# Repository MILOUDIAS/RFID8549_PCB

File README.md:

# RFID8549_PCB
PCB for bring-up testing of our RFID chip in ihp sg13g2 pdk

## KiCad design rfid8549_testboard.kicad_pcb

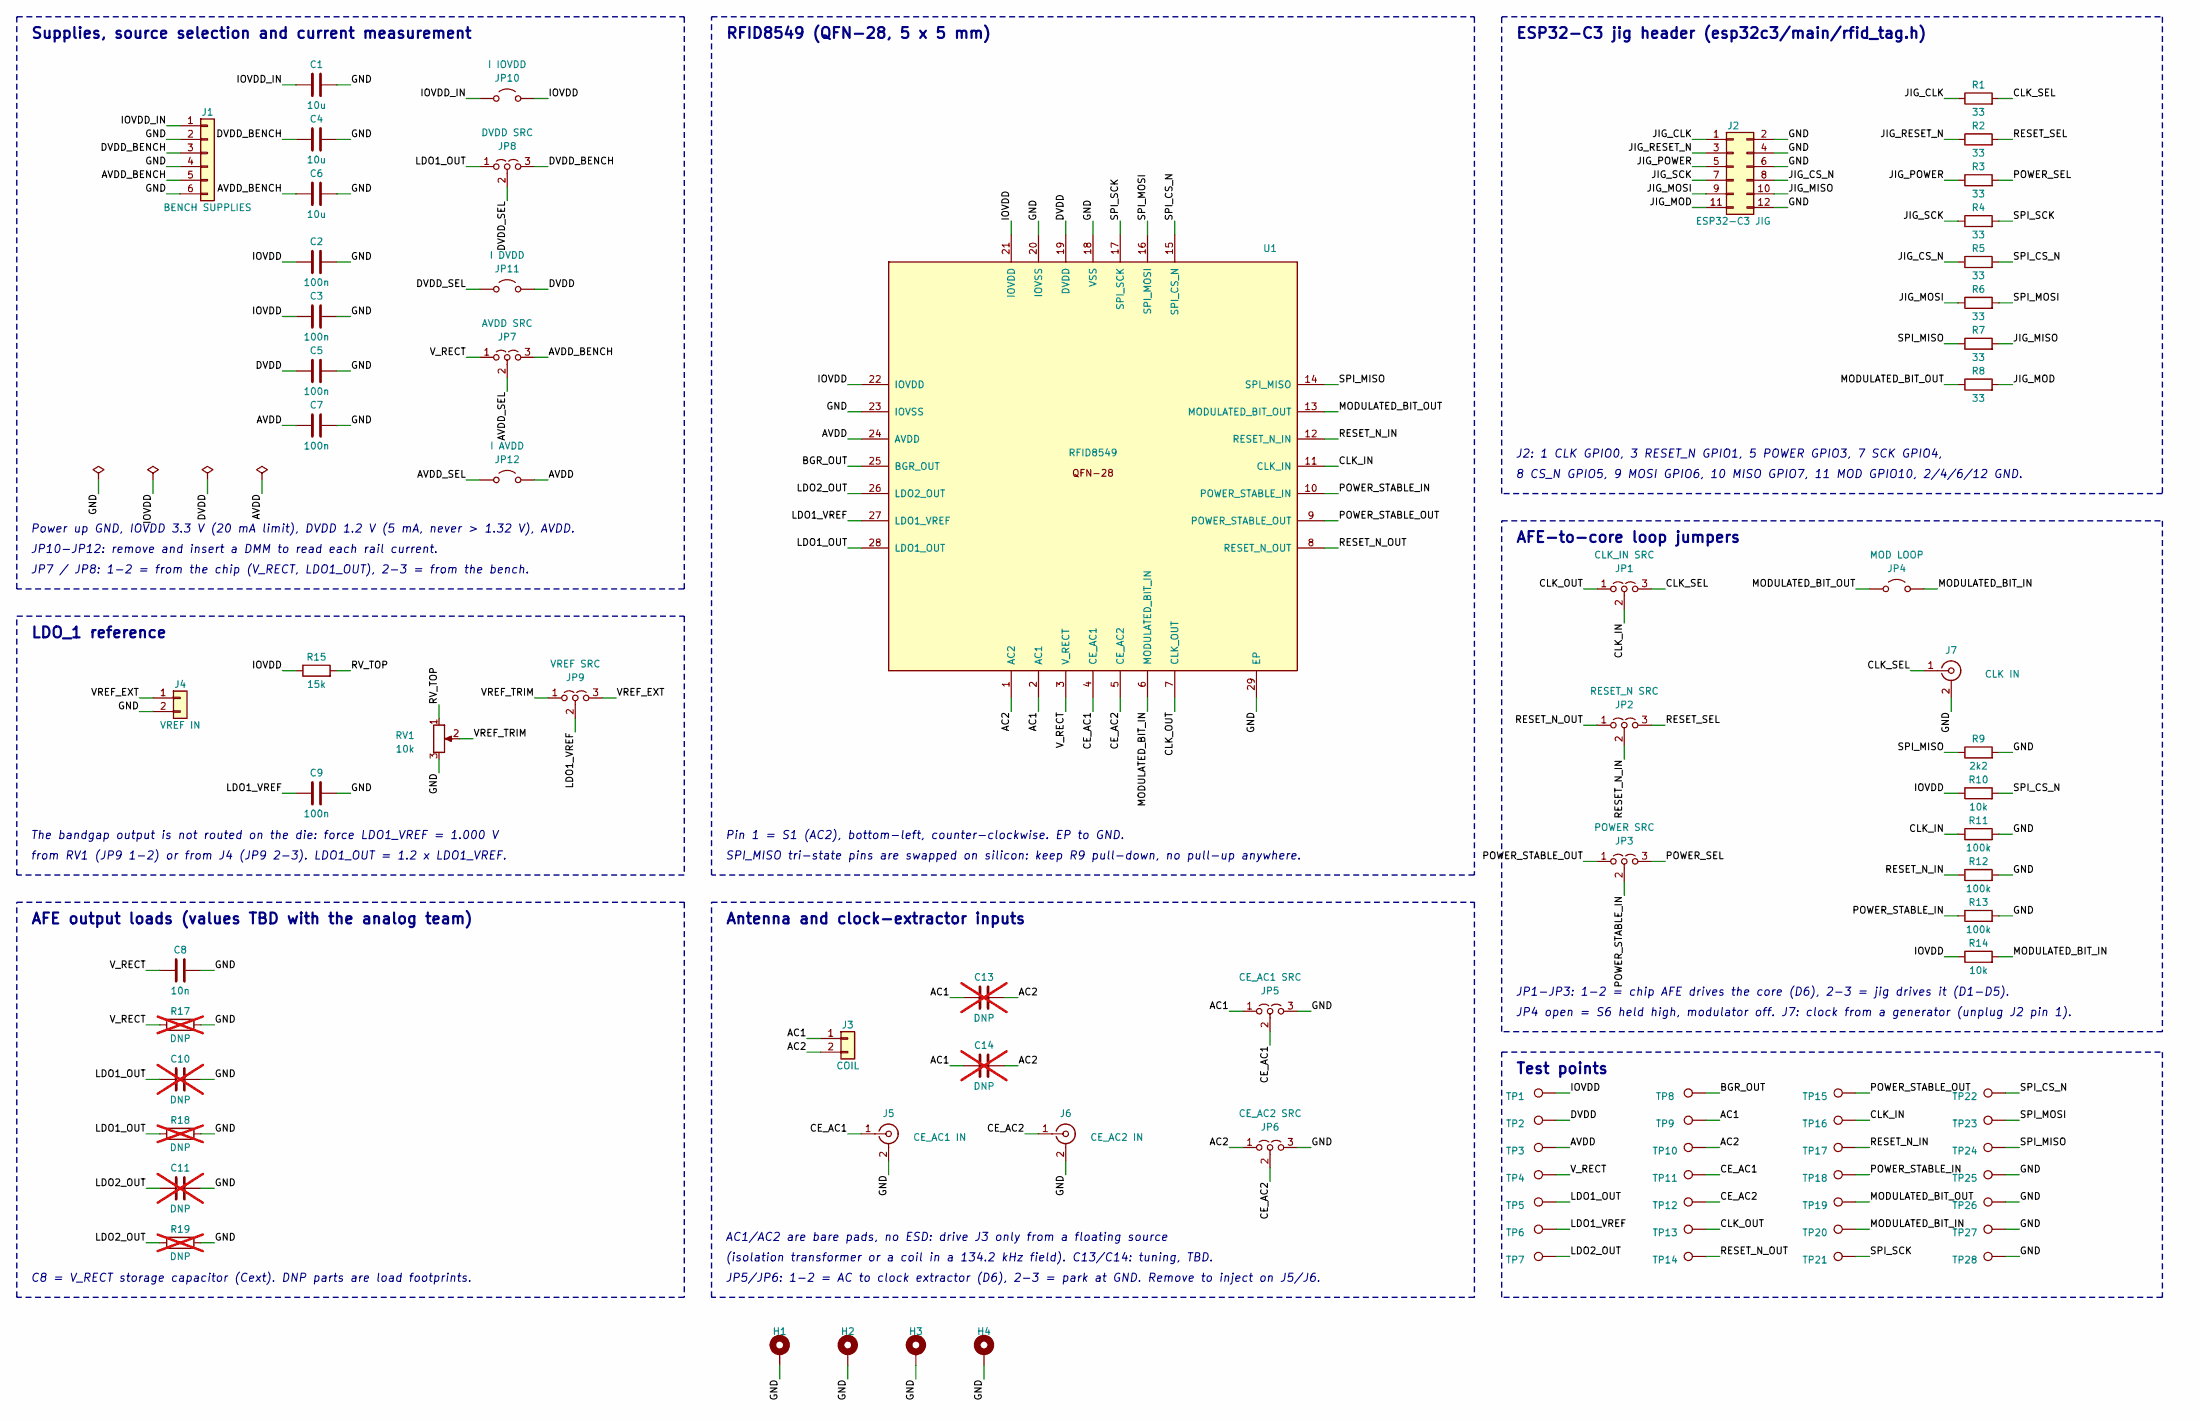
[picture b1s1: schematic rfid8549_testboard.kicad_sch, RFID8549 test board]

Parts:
C1, C4, C6: 10u; C_1206_3216Metric
C2, C3, C5, C7, C9: 100n; C_0805_2012Metric
C8: 10n; C_0805_2012Metric
C10, C11, C13, C14: DNP; C_0805_2012Metric; not fitted
H1, H2, H3, H4: M3; MountingHole_3.2mm_M3_Pad_Via
J1: BENCH SUPPLIES; TerminalBlock_Phoenix_MKDS-1,5-6_1x06_P5.00mm_Horizontal
J2: ESP32-C3 JIG; PinHeader_2x06_P2.54mm_Vertical
J3: COIL; TerminalBlock_Phoenix_MKDS-1,5-2_1x02_P5.00mm_Horizontal
J4: VREF IN; PinHeader_1x02_P2.54mm_Vertical
J5: CE_AC1 IN; SMA_Amphenol_132134_Vertical
J6: CE_AC2 IN; SMA_Amphenol_132134_Vertical
J7: CLK IN; SMA_Amphenol_132134_Vertical
JP1: CLK_IN SRC; PinHeader_1x03_P2.54mm_Vertical
JP2: RESET_N SRC; PinHeader_1x03_P2.54mm_Vertical
JP3: POWER SRC; PinHeader_1x03_P2.54mm_Vertical
JP4: MOD LOOP; PinHeader_1x02_P2.54mm_Vertical
JP5: CE_AC1 SRC; PinHeader_1x03_P2.54mm_Vertical
JP6: CE_AC2 SRC; PinHeader_1x03_P2.54mm_Vertical
JP7: AVDD SRC; PinHeader_1x03_P2.54mm_Vertical
JP8: DVDD SRC; PinHeader_1x03_P2.54mm_Vertical
JP9: VREF SRC; PinHeader_1x03_P2.54mm_Vertical
JP10: I IOVDD; PinHeader_1x02_P2.54mm_Vertical
JP11: I DVDD; PinHeader_1x02_P2.54mm_Vertical
JP12: I AVDD; PinHeader_1x02_P2.54mm_Vertical
R1, R2, R3, R4, R5, R6, R7, R8: 33; R_0805_2012Metric
R9: 2k2; R_0805_2012Metric
R10, R14: 10k; R_0805_2012Metric
R11, R12, R13: 100k; R_0805_2012Metric
R15: 15k; R_0805_2012Metric
R17, R18, R19: DNP; R_0805_2012Metric; not fitted
RV1: 10k; Potentiometer_Bourns_3296W_Vertical
TP1: IOVDD; TestPoint_Keystone_5000-5004_Miniature
TP2: DVDD; TestPoint_Keystone_5000-5004_Miniature
TP3: AVDD; TestPoint_Keystone_5000-5004_Miniature
TP4: V_RECT; TestPoint_Keystone_5000-5004_Miniature
TP5: LDO1_OUT; TestPoint_Keystone_5000-5004_Miniature
TP6: LDO1_VREF; TestPoint_Keystone_5000-5004_Miniature
TP7: LDO2_OUT; TestPoint_Keystone_5000-5004_Miniature
TP8: BGR_OUT; TestPoint_Keystone_5000-5004_Miniature
TP9: AC1; TestPoint_Keystone_5000-5004_Miniature
TP10: AC2; TestPoint_Keystone_5000-5004_Miniature
TP11: CE_AC1; TestPoint_Keystone_5000-5004_Miniature
TP12: CE_AC2; TestPoint_Keystone_5000-5004_Miniature
TP13: CLK_OUT; TestPoint_Keystone_5000-5004_Miniature
TP14: RESET_N_OUT; TestPoint_Keystone_5000-5004_Miniature
TP15: POWER_STABLE_OUT; TestPoint_Keystone_5000-5004_Miniature
TP16: CLK_IN; TestPoint_Keystone_5000-5004_Miniature
TP17: RESET_N_IN; TestPoint_Keystone_5000-5004_Miniature
TP18: POWER_STABLE_IN; TestPoint_Keystone_5000-5004_Miniature
TP19: MODULATED_BIT_OUT; TestPoint_Keystone_5000-5004_Miniature
TP20: MODULATED_BIT_IN; TestPoint_Keystone_5000-5004_Miniature
TP21: SPI_SCK; TestPoint_Keystone_5000-5004_Miniature
TP22: SPI_CS_N; TestPoint_Keystone_5000-5004_Miniature
TP23: SPI_MOSI; TestPoint_Keystone_5000-5004_Miniature
TP24: SPI_MISO; TestPoint_Keystone_5000-5004_Miniature
TP25, TP26, TP27, TP28: GND; TestPoint_Keystone_5000-5004_Miniature
U1: RFID8549; QFN-28-1EP_5x5mm_P0.5mm_EP3.35x3.35mm_ThermalVias

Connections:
AC1: C13.1, C14.1, J3.1, JP5.1 (A), TP9.1, U1.2 (AC1)
AC2: C13.2, C14.2, J3.2, JP6.1 (A), TP10.1, U1.1 (AC2)
AVDD: C7.1, JP12.2 (B), TP3.1, U1.24 (AVDD)
AVDD_BENCH: C6.1, J1.5, JP7.3 (B)
AVDD_SEL: JP7.2 (C), JP12.1 (A)
BGR_OUT: TP8.1, U1.25 (BGR_OUT)
CE_AC1: J5.1 (In), JP5.2 (C), TP11.1, U1.4 (CE_AC1)
CE_AC2: J6.1 (In), JP6.2 (C), TP12.1, U1.5 (CE_AC2)
CLK_IN: JP1.2 (C), R11.1, TP16.1, U1.11 (CLK_IN)
CLK_OUT: JP1.1 (A), TP13.1, U1.7 (CLK_OUT)
CLK_SEL: J7.1 (In), JP1.3 (B), R1.2
DVDD: C5.1, JP11.2 (B), TP2.1, U1.19 (DVDD)
DVDD_BENCH: C4.1, J1.3, JP8.3 (B)
DVDD_SEL: JP8.2 (C), JP11.1 (A)
GND: C1.2, C2.2, C3.2, C4.2, C5.2, C6.2, C7.2, C8.2, C9.2, C10.2, C11.2, H1.1, H2.1, H3.1, H4.1, J1.2, J1.4, J1.6, J2.2, J2.4, J2.6, J2.12, J4.2, J5.2 (Ext), J6.2 (Ext), J7.2 (Ext), JP5.3 (B), JP6.3 (B), R9.2, R11.2, R12.2, R13.2, R17.2, R18.2, R19.2, RV1.3, TP25.1, TP26.1, TP27.1, TP28.1, U1.18 (VSS), U1.20 (IOVSS), U1.23 (IOVSS), U1.29 (EP)
IOVDD: C2.1, C3.1, JP10.2 (B), R10.1, R14.1, R15.1, TP1.1, U1.21 (IOVDD), U1.22 (IOVDD)
IOVDD_IN: C1.1, J1.1, JP10.1 (A)
JIG_CLK: J2.1, R1.1
JIG_CS_N: J2.8, R5.1
JIG_MISO: J2.10, R7.2
JIG_MOD: J2.11, R8.2
JIG_MOSI: J2.9, R6.1
JIG_POWER: J2.5, R3.1
JIG_RESET_N: J2.3, R2.1
JIG_SCK: J2.7, R4.1
LDO1_OUT: C10.1, JP8.1 (A), R18.1, TP5.1, U1.28 (LDO1_OUT)
LDO1_VREF: C9.1, JP9.2 (C), TP6.1, U1.27 (LDO1_VREF)
LDO2_OUT: C11.1, R19.1, TP7.1, U1.26 (LDO2_OUT)
MODULATED_BIT_IN: JP4.2 (B), R14.2, TP20.1, U1.6 (MODULATED_BIT_IN)
MODULATED_BIT_OUT: JP4.1 (A), R8.1, TP19.1, U1.13 (MODULATED_BIT_OUT)
POWER_SEL: JP3.3 (B), R3.2
POWER_STABLE_IN: JP3.2 (C), R13.1, TP18.1, U1.10 (POWER_STABLE_IN)
POWER_STABLE_OUT: JP3.1 (A), TP15.1, U1.9 (POWER_STABLE_OUT)
RESET_N_IN: JP2.2 (C), R12.1, TP17.1, U1.12 (RESET_N_IN)
RESET_N_OUT: JP2.1 (A), TP14.1, U1.8 (RESET_N_OUT)
RESET_SEL: JP2.3 (B), R2.2
RV_TOP: R15.2, RV1.1
SPI_CS_N: R5.2, R10.2, TP22.1, U1.15 (SPI_CS_N)
SPI_MISO: R7.1, R9.1, TP24.1, U1.14 (SPI_MISO)
SPI_MOSI: R6.2, TP23.1, U1.16 (SPI_MOSI)
SPI_SCK: R4.2, TP21.1, U1.17 (SPI_SCK)
VREF_EXT: J4.1, JP9.3 (B)
VREF_TRIM: JP9.1 (A), RV1.2
V_RECT: C8.1, JP7.1 (A), R17.1, TP4.1, U1.3 (V_RECT)

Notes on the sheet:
Supplies, source selection and current measurement
Power up GND, IOVDD 3.3 V (20 mA limit), DVDD 1.2 V (5 mA, never > 1.32 V), AVDD.
JP10-JP12: remove and insert a DMM to read each rail current.
JP7 / JP8: 1-2 = from the chip (V_RECT, LDO1_OUT), 2-3 = from the bench.
LDO_1 reference
The bandgap output is not routed on the die: force LDO1_VREF = 1.000 V
from RV1 (JP9 1-2) or from J4 (JP9 2-3). LDO1_OUT = 1.2 x LDO1_VREF.
AFE output loads (values TBD with the analog team)
C8 = V_RECT storage capacitor (Cext). DNP parts are load footprints.
RFID8549 (QFN-28, 5 x 5 mm)
Pin 1 = S1 (AC2), bottom-left, counter-clockwise. EP to GND.
SPI_MISO tri-state pins are swapped on silicon: keep R9 pull-down, no pull-up anywhere.
Antenna and clock-extractor inputs
AC1/AC2 are bare pads, no ESD: drive J3 only from a floating source
(isolation transformer or a coil in a 134.2 kHz field). C13/C14: tuning, TBD.
JP5/JP6: 1-2 = AC to clock extractor (D6), 2-3 = park at GND. Remove to inject on J5/J6.
ESP32-C3 jig header (esp32c3/main/rfid_tag.h)
J2: 1 CLK GPIO0, 3 RESET_N GPIO1, 5 POWER GPIO3, 7 SCK GPIO4,
8 CS_N GPIO5, 9 MOSI GPIO6, 10 MISO GPIO7, 11 MOD GPIO10, 2/4/6/12 GND.
AFE-to-core loop jumpers
JP1-JP3: 1-2 = chip AFE drives the core (D6), 2-3 = jig drives it (D1-D5).
JP4 open = S6 held high, modulator off. J7: clock from a generator (unplug J2 pin 1).
Test points

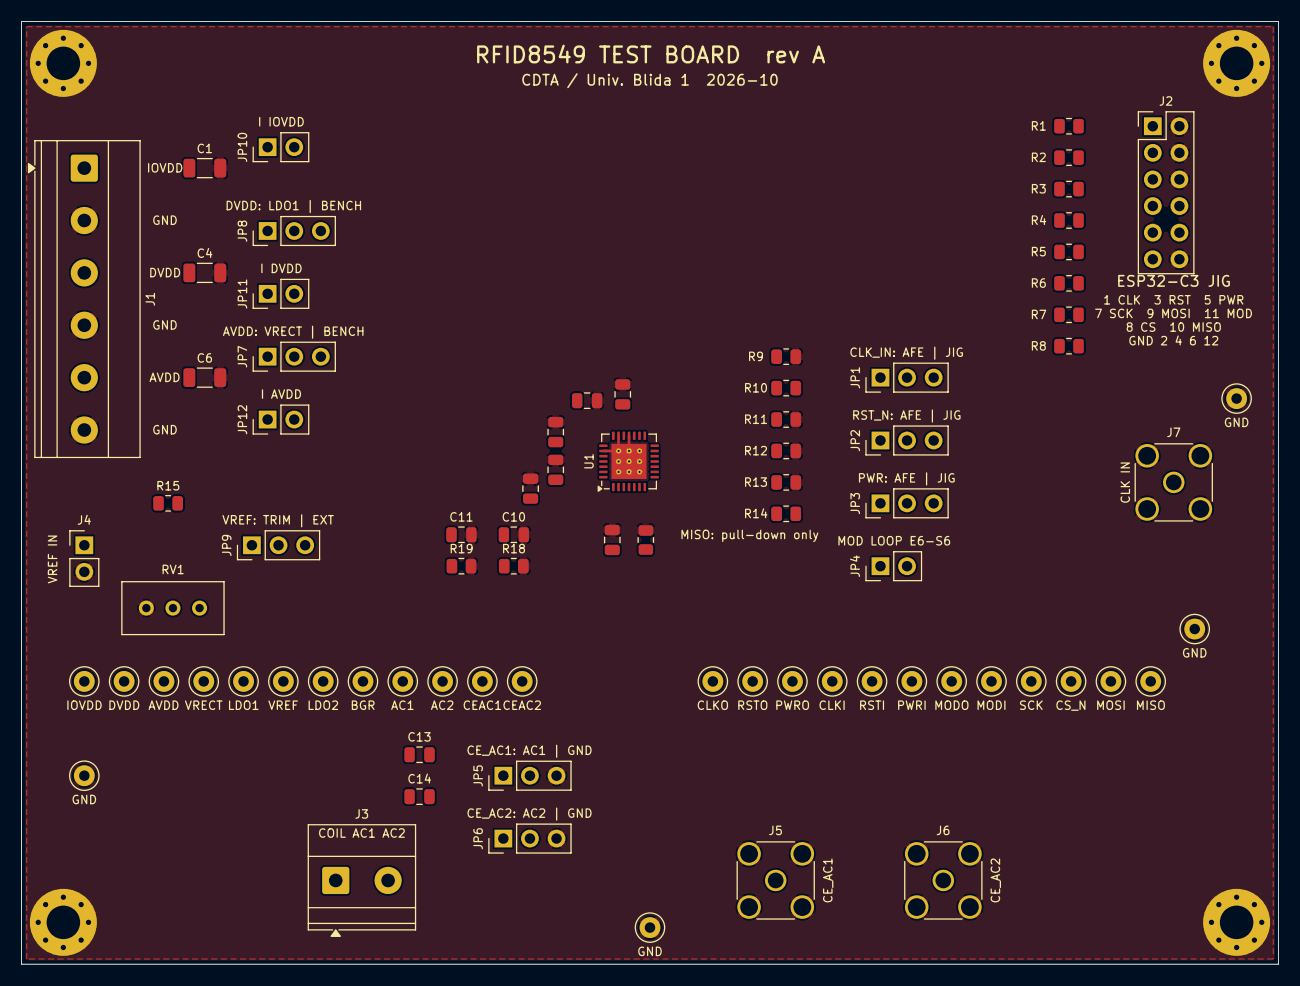
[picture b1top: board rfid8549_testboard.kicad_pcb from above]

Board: 2 copper layers, 120.0 x 90.0 mm, 84 parts (0 on the bottom side), 44 nets.

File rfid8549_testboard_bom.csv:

"Refs","Value","Footprint","Qty","DNP"
"C1,C4,C6","10u","Capacitor_SMD:C_1206_3216Metric","3",""
"C2,C3,C5,C7,C9","100n","Capacitor_SMD:C_0805_2012Metric","5",""
"C8","10n","Capacitor_SMD:C_0805_2012Metric","1",""
"H1-H4","M3","MountingHole:MountingHole_3.2mm_M3_Pad_Via","4",""
"J1","BENCH SUPPLIES","TerminalBlock_Phoenix:TerminalBlock_Phoenix_MKDS-1,5-6_1x06_P5.00mm_Horizontal","1",""
"J2","ESP32-C3 JIG","Connector_PinHeader_2.54mm:PinHeader_2x06_P2.54mm_Vertical","1",""
"J3","COIL","TerminalBlock_Phoenix:TerminalBlock_Phoenix_MKDS-1,5-2_1x02_P5.00mm_Horizontal","1",""
"J4","VREF IN","Connector_PinHeader_2.54mm:PinHeader_1x02_P2.54mm_Vertical","1",""
"J5","CE_AC1 IN","Connector_Coaxial:SMA_Amphenol_132134_Vertical","1",""
"J6","CE_AC2 IN","Connector_Coaxial:SMA_Amphenol_132134_Vertical","1",""
"J7","CLK IN","Connector_Coaxial:SMA_Amphenol_132134_Vertical","1",""
"JP1","CLK_IN SRC","Connector_PinHeader_2.54mm:PinHeader_1x03_P2.54mm_Vertical","1",""
"JP2","RESET_N SRC","Connector_PinHeader_2.54mm:PinHeader_1x03_P2.54mm_Vertical","1",""
"JP3","POWER SRC","Connector_PinHeader_2.54mm:PinHeader_1x03_P2.54mm_Vertical","1",""
"JP4","MOD LOOP","Connector_PinHeader_2.54mm:PinHeader_1x02_P2.54mm_Vertical","1",""
"JP5","CE_AC1 SRC","Connector_PinHeader_2.54mm:PinHeader_1x03_P2.54mm_Vertical","1",""
"JP6","CE_AC2 SRC","Connector_PinHeader_2.54mm:PinHeader_1x03_P2.54mm_Vertical","1",""
"JP7","AVDD SRC","Connector_PinHeader_2.54mm:PinHeader_1x03_P2.54mm_Vertical","1",""
"JP8","DVDD SRC","Connector_PinHeader_2.54mm:PinHeader_1x03_P2.54mm_Vertical","1",""
"JP9","VREF SRC","Connector_PinHeader_2.54mm:PinHeader_1x03_P2.54mm_Vertical","1",""
"JP10","I IOVDD","Connector_PinHeader_2.54mm:PinHeader_1x02_P2.54mm_Vertical","1",""
"JP11","I DVDD","Connector_PinHeader_2.54mm:PinHeader_1x02_P2.54mm_Vertical","1",""
"JP12","I AVDD","Connector_PinHeader_2.54mm:PinHeader_1x02_P2.54mm_Vertical","1",""
"R1-R8","33","Resistor_SMD:R_0805_2012Metric","8",""
"R9","2k2","Resistor_SMD:R_0805_2012Metric","1",""
"R10,R14","10k","Resistor_SMD:R_0805_2012Metric","2",""
"R11-R13","100k","Resistor_SMD:R_0805_2012Metric","3",""
"R15","15k","Resistor_SMD:R_0805_2012Metric","1",""
"RV1","10k","Potentiometer_THT:Potentiometer_Bourns_3296W_Vertical","1",""
"TP1","IOVDD","TestPoint:TestPoint_Keystone_5000-5004_Miniature","1",""
"TP2","DVDD","TestPoint:TestPoint_Keystone_5000-5004_Miniature","1",""
"TP3","AVDD","TestPoint:TestPoint_Keystone_5000-5004_Miniature","1",""
"TP4","V_RECT","TestPoint:TestPoint_Keystone_5000-5004_Miniature","1",""
"TP5","LDO1_OUT","TestPoint:TestPoint_Keystone_5000-5004_Miniature","1",""
"TP6","LDO1_VREF","TestPoint:TestPoint_Keystone_5000-5004_Miniature","1",""
"TP7","LDO2_OUT","TestPoint:TestPoint_Keystone_5000-5004_Miniature","1",""
"TP8","BGR_OUT","TestPoint:TestPoint_Keystone_5000-5004_Miniature","1",""
"TP9","AC1","TestPoint:TestPoint_Keystone_5000-5004_Miniature","1",""
"TP10","AC2","TestPoint:TestPoint_Keystone_5000-5004_Miniature","1",""
"TP11","CE_AC1","TestPoint:TestPoint_Keystone_5000-5004_Miniature","1",""
"TP12","CE_AC2","TestPoint:TestPoint_Keystone_5000-5004_Miniature","1",""
"TP13","CLK_OUT","TestPoint:TestPoint_Keystone_5000-5004_Miniature","1",""
"TP14","RESET_N_OUT","TestPoint:TestPoint_Keystone_5000-5004_Miniature","1",""
"TP15","POWER_STABLE_OUT","TestPoint:TestPoint_Keystone_5000-5004_Miniature","1",""
"TP16","CLK_IN","TestPoint:TestPoint_Keystone_5000-5004_Miniature","1",""
"TP17","RESET_N_IN","TestPoint:TestPoint_Keystone_5000-5004_Miniature","1",""
"TP18","POWER_STABLE_IN","TestPoint:TestPoint_Keystone_5000-5004_Miniature","1",""
"TP19","MODULATED_BIT_OUT","TestPoint:TestPoint_Keystone_5000-5004_Miniature","1",""
"TP20","MODULATED_BIT_IN","TestPoint:TestPoint_Keystone_5000-5004_Miniature","1",""
"TP21","SPI_SCK","TestPoint:TestPoint_Keystone_5000-5004_Miniature","1",""
"TP22","SPI_CS_N","TestPoint:TestPoint_Keystone_5000-5004_Miniature","1",""
"TP23","SPI_MOSI","TestPoint:TestPoint_Keystone_5000-5004_Miniature","1",""
"TP24","SPI_MISO","TestPoint:TestPoint_Keystone_5000-5004_Miniature","1",""
"TP25-TP28","GND","TestPoint:TestPoint_Keystone_5000-5004_Miniature","4",""
"U1","RFID8549","Package_DFN_QFN:QFN-28-1EP_5x5mm_P0.5mm_EP3.35x3.35mm_ThermalVias","1",""
